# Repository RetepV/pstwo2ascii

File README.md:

# pstwo2ascii
My rendition of Jim Brain/RETRO Innovations **PS2Encoder**.

The original (copyrighted by Jim Brain and RETRO Innovations) can be found here: https://github.com/go4retro/PS2Encoder.

I decided to make the board USB powered, and add a "real" RS-232 V24 interface. Most vintage computers cannot work with 0V/5V, but need positive and negative voltages. And some old vintage computers output +12V and -12V, and wil very likely blow up the ATMEGA's ports. Lastly, I used an ATMEGA328 instead of an ATMEGA88, just because I have a few of those lying around.

I decided to make it in SMD, to keep the boards small. I took hand-solderability into account as much as possible. Of course the connectors mostly dictate the final size of the board, and t.b.h. I think that if I had used PTH components, the board would not be much larger. But there you go: it's my design and I can do what I want to. ;)

**Note: this is a WIP and has not been tested yet, prototypes have not even been created yet.**

The base design and the software is not mine, but created and copyrighted (2008-2018) by Jim Brain / RETRO Innovations. I took the base design, redesigned it to make a full-fledged board powered by USB and having a real RS-232 V24 interface using a MAX232, and named it **pstwo2ascii**. This board is meant to be used with the firmware of **PS2Encoder**, which can be found here: https://github.com/go4retro/PS2Encoder/tree/master. Big thanks and kudos to Jim Brain for his work!

Please note that **pstwo2ascii** is covered under GPLv3, while **PS2Encoder** is covered under GPLv2. **pstwo2ascii** only applies to the hardware designs that you can find in this repository.

## Licenses

### PS2Encoder

Copyright Jim Brain and RETRO Innovations, 2008-2018

These files are free designs; you can redistribute them and/or modify them under the terms of the GNU General Public License, version 2 as published by the Free Software Foundation.

These files are distributed in the hope that they will be useful, but WITHOUT ANY WARRANTY; without even the implied warranty of MERCHANTABILITY or FITNESS FOR A PARTICULAR PURPOSE. See the GNU General Public License for more details.

You should have received a copy of the GNU General Public License along with these files; if not, write to the Free Software Foundation, Inc., 51 Franklin Street, Fifth Floor, Boston, MA 02110-1301 USA.

### pstwo2ascii

Copyright Sporos Tech, Peter de Vroomen, 2025

**pstwo2ascii** is free software: you can redistribute it and/or modify it under the terms of the GNU General Public License as published by the Free Software Foundation, either version 3 of the License, or (at your option) any later version.

**pstwo2ascii** is distributed in the hope that it will be useful, but WITHOUT ANY WARRANTY; without even the implied warranty of MERCHANTABILITY or FITNESS FOR A PARTICULAR PURPOSE. See the GNU General Public License for more details.

You should have received a copy of the GNU General Public License along with **pstwo2ascii**. If not, see <https://www.gnu.org/licenses/>.

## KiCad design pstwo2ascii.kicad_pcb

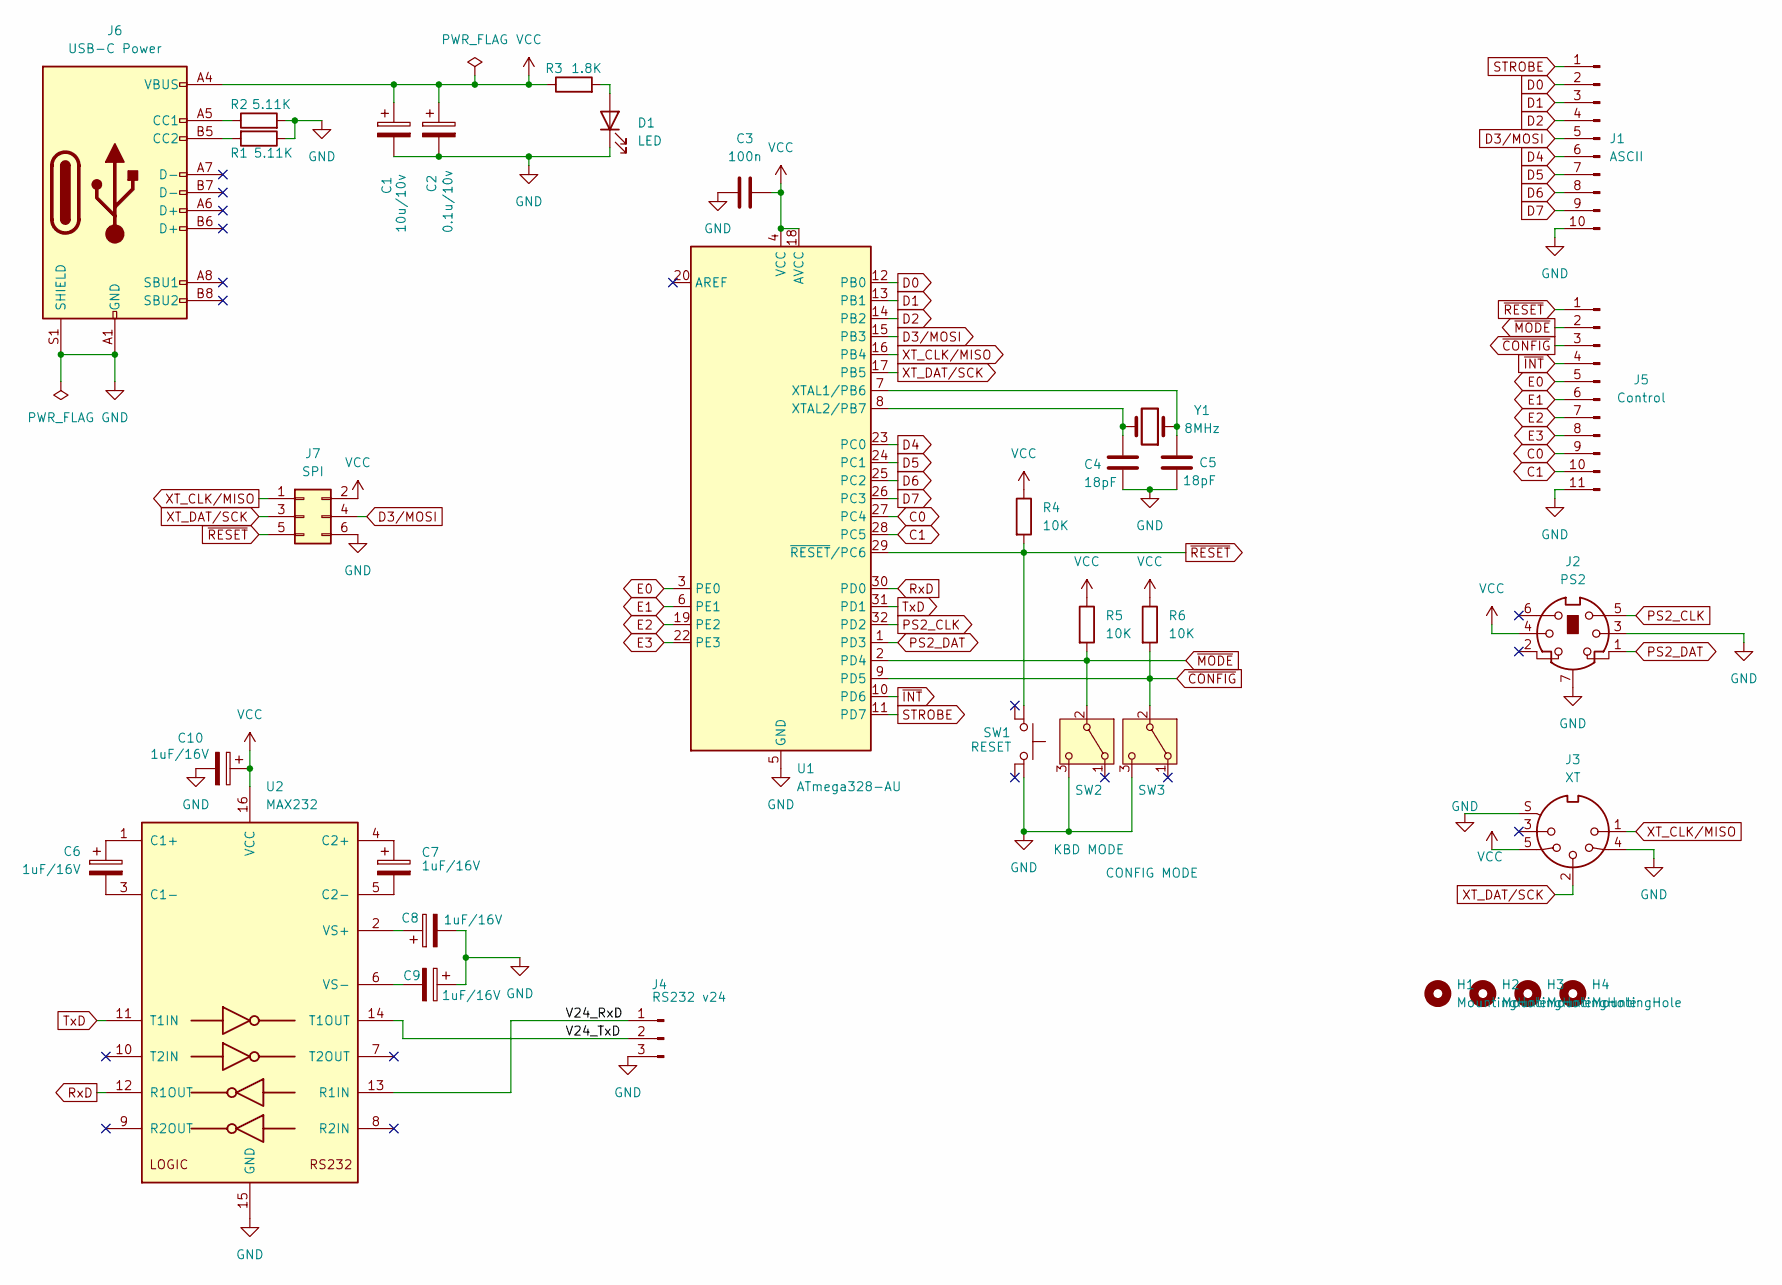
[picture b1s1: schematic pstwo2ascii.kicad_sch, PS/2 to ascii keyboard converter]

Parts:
C1: 10u/10v; CP_EIA-3216-18_Kemet-A_Pad1.58x1.35mm_HandSolder
C2: 0.1u/10v; CP_EIA-3216-18_Kemet-A_Pad1.58x1.35mm_HandSolder
C3: 100n; C_0603_1608Metric_Pad1.08x0.95mm_HandSolder
C4, C5: 18pF; C_0603_1608Metric_Pad1.08x0.95mm_HandSolder
C6, C7, C8, C9, C10: 1uF/16V; CP_EIA-3216-12_Kemet-S_Pad1.58x1.35mm_HandSolder
D1: LED; LED_0603_1608Metric_Pad1.05x0.95mm_HandSolder
H1, H2, H3, H4: MountingHole; MountingHole_3.2mm_M3
J1: ASCII; PinHeader_1x10_P2.54mm_Vertical
J2: PS2; Connector_Mini-DIN_Female_6Pin_2rows
J3: XT; DIN-5-180
J4: RS232 v24; PinHeader_1x03_P2.54mm_Vertical
J5: Control; PinHeader_1x11_P2.54mm_Vertical
J6: USB-C Power; USB_C_Receptacle_Molex_213716-0001
J7: SPI; PinHeader_2x03_P2.54mm_Vertical
R1, R2: 5.11K; R_0603_1608Metric_Pad0.98x0.95mm_HandSolder
R3: 1.8K; R_0603_1608Metric_Pad0.98x0.95mm_HandSolder
R4, R5, R6: 10K; R_0603_1608Metric_Pad0.98x0.95mm_HandSolder
SW1: RESET; SW_SPST_Omron_B3FS-100xP_4P
SW2: KBD MODE; CL-SB-12B-0x SPDT switch
SW3: CONFIG MODE; CL-SB-12B-0x SPDT switch
U1: ATmega328-AU; TQFP-32_7x7mm_P0.8mm
U2: MAX232; SOIC-16_4.55x10.3mm_P1.27mm
Y1: 8MHz; Crystal_SMD_HC49-SD

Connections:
/V24_RxD: J4.1, U2.13 (R1IN)
/V24_TxD: J4.2, U2.14 (T1OUT)
C0: J5.9, U1.27 (PC4)
C1: J5.10, U1.28 (PC5)
D0: J1.2, U1.12 (PB0)
D1: J1.3, U1.13 (PB1)
D2: J1.4, U1.14 (PB2)
D3/MOSI: J1.5, J7.4, U1.15 (PB3)
D4: J1.6, U1.23 (PC0)
D5: J1.7, U1.24 (PC1)
D6: J1.8, U1.25 (PC2)
D7: J1.9, U1.26 (PC3)
E0: J5.5, U1.3 (PE0)
E1: J5.6, U1.6 (PE1)
E2: J5.7, U1.19 (PE2)
E3: J5.8, U1.22 (PE3)
GND: C1.2, C2.2, C3.2, C4.2, C5.2, C8.2, C9.1, C10.2, D1.1 (K), J1.10, J2.3, J2.7, J3.4, J3.S, J4.3, J5.11, J6.A1 (GND), J6.A12 (GND), J6.B1 (GND), J6.B12 (GND), J6.S1 (SHIELD), J7.6, R1.1, R2.2, SW1.3, SW2.3 (C), SW3.3 (C), U1.5 (GND), U1.21 (GND), U2.15 (GND)
unnamed: D1.2 (A), R3.2
unnamed: J6.A5 (CC1), R2.1
unnamed: J6.B5 (CC2), R1.2
unnamed: C5.1, U1.7 (XTAL1/PB6), Y1.1
unnamed: C4.1, U1.8 (XTAL2/PB7), Y1.2
unnamed: C6.1, U2.1 (C1+)
unnamed: C6.2, U2.3 (C1-)
unnamed: C7.1, U2.4 (C2+)
unnamed: C7.2, U2.5 (C2-)
unnamed: C8.1, U2.2 (VS+)
unnamed: C9.2, U2.6 (VS-)
PS2_CLK: J2.5, U1.32 (PD2)
PS2_DAT: J2.1, U1.1 (PD3)
RxD: U1.30 (PD0), U2.12 (R1OUT)
STROBE: J1.1, U1.11 (PD7)
TxD: U1.31 (PD1), U2.11 (T1IN)
VCC: C1.1, C2.1, C3.1, C10.1, J2.4, J3.5, J6.A4 (VBUS), J6.A9 (VBUS), J6.B4 (VBUS), J6.B9 (VBUS), J7.2, R3.1, R4.1, R5.1, R6.1, U1.4 (VCC), U1.18 (AVCC), U2.16 (VCC)
XT_CLK/MISO: J3.1, J7.1, U1.16 (PB4)
XT_DAT/SCK: J3.2, J7.3, U1.17 (PB5)
~CONFIG: J5.3, R6.2, SW3.2 (B), U1.9 (PD5)
~INT: J5.4, U1.10 (PD6)
~MODE: J5.2, R5.2, SW2.2 (B), U1.2 (PD4)
~RESET: J5.1, J7.5, R4.2, SW1.1, U1.29 (~RESET/PC6)

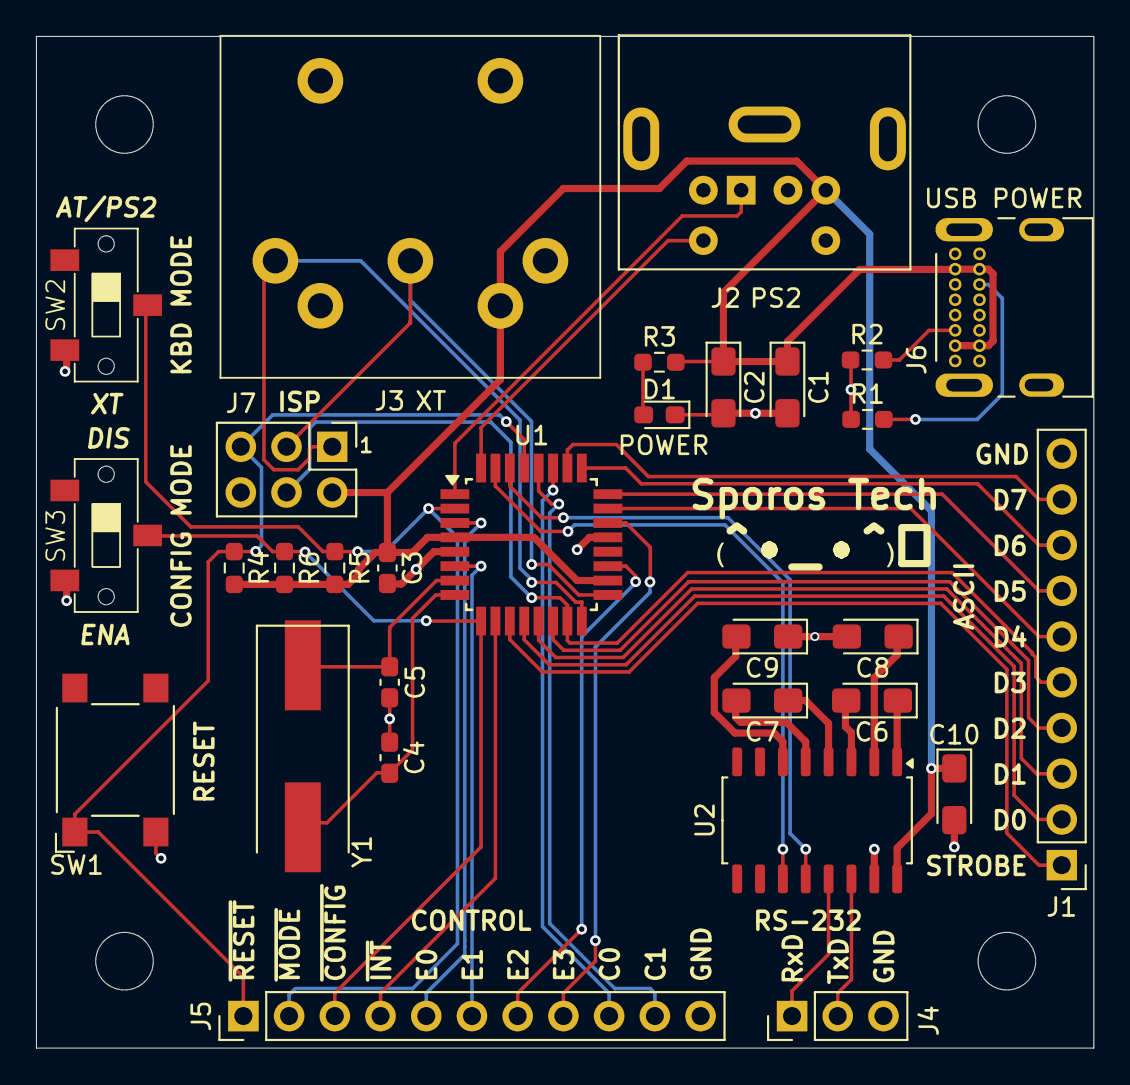
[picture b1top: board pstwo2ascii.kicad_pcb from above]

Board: 2 copper layers, 58.7 x 56.2 mm, 34 parts (0 on the bottom side), 40 nets.

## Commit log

2025-05-14 Initial commit of pstwo2ascii PCB
2025-05-14 Improvements. Added 3D models, changed pushbuttons to slider switches. Clearer text.
2025-05-15 Added GPLv3 license file. Also some new backup created by Kicad.
2025-05-15 Update "pretty" files.
2025-05-15 Add a few extra GND pins on the pin connectors. Also added copyright information in the sheets. Also updated pretty files.
2025-05-15 Some small improvements, and assigning datasheets.
2025-05-16 Some final tweaks, changing the labels of the buttons and switches.

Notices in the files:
pstwo2ascii.kicad_pcb:
Copyright 2025, Sporos Tech, Peter de Vroomen
Licensed under GPLv3
Copyright 2008-2018
